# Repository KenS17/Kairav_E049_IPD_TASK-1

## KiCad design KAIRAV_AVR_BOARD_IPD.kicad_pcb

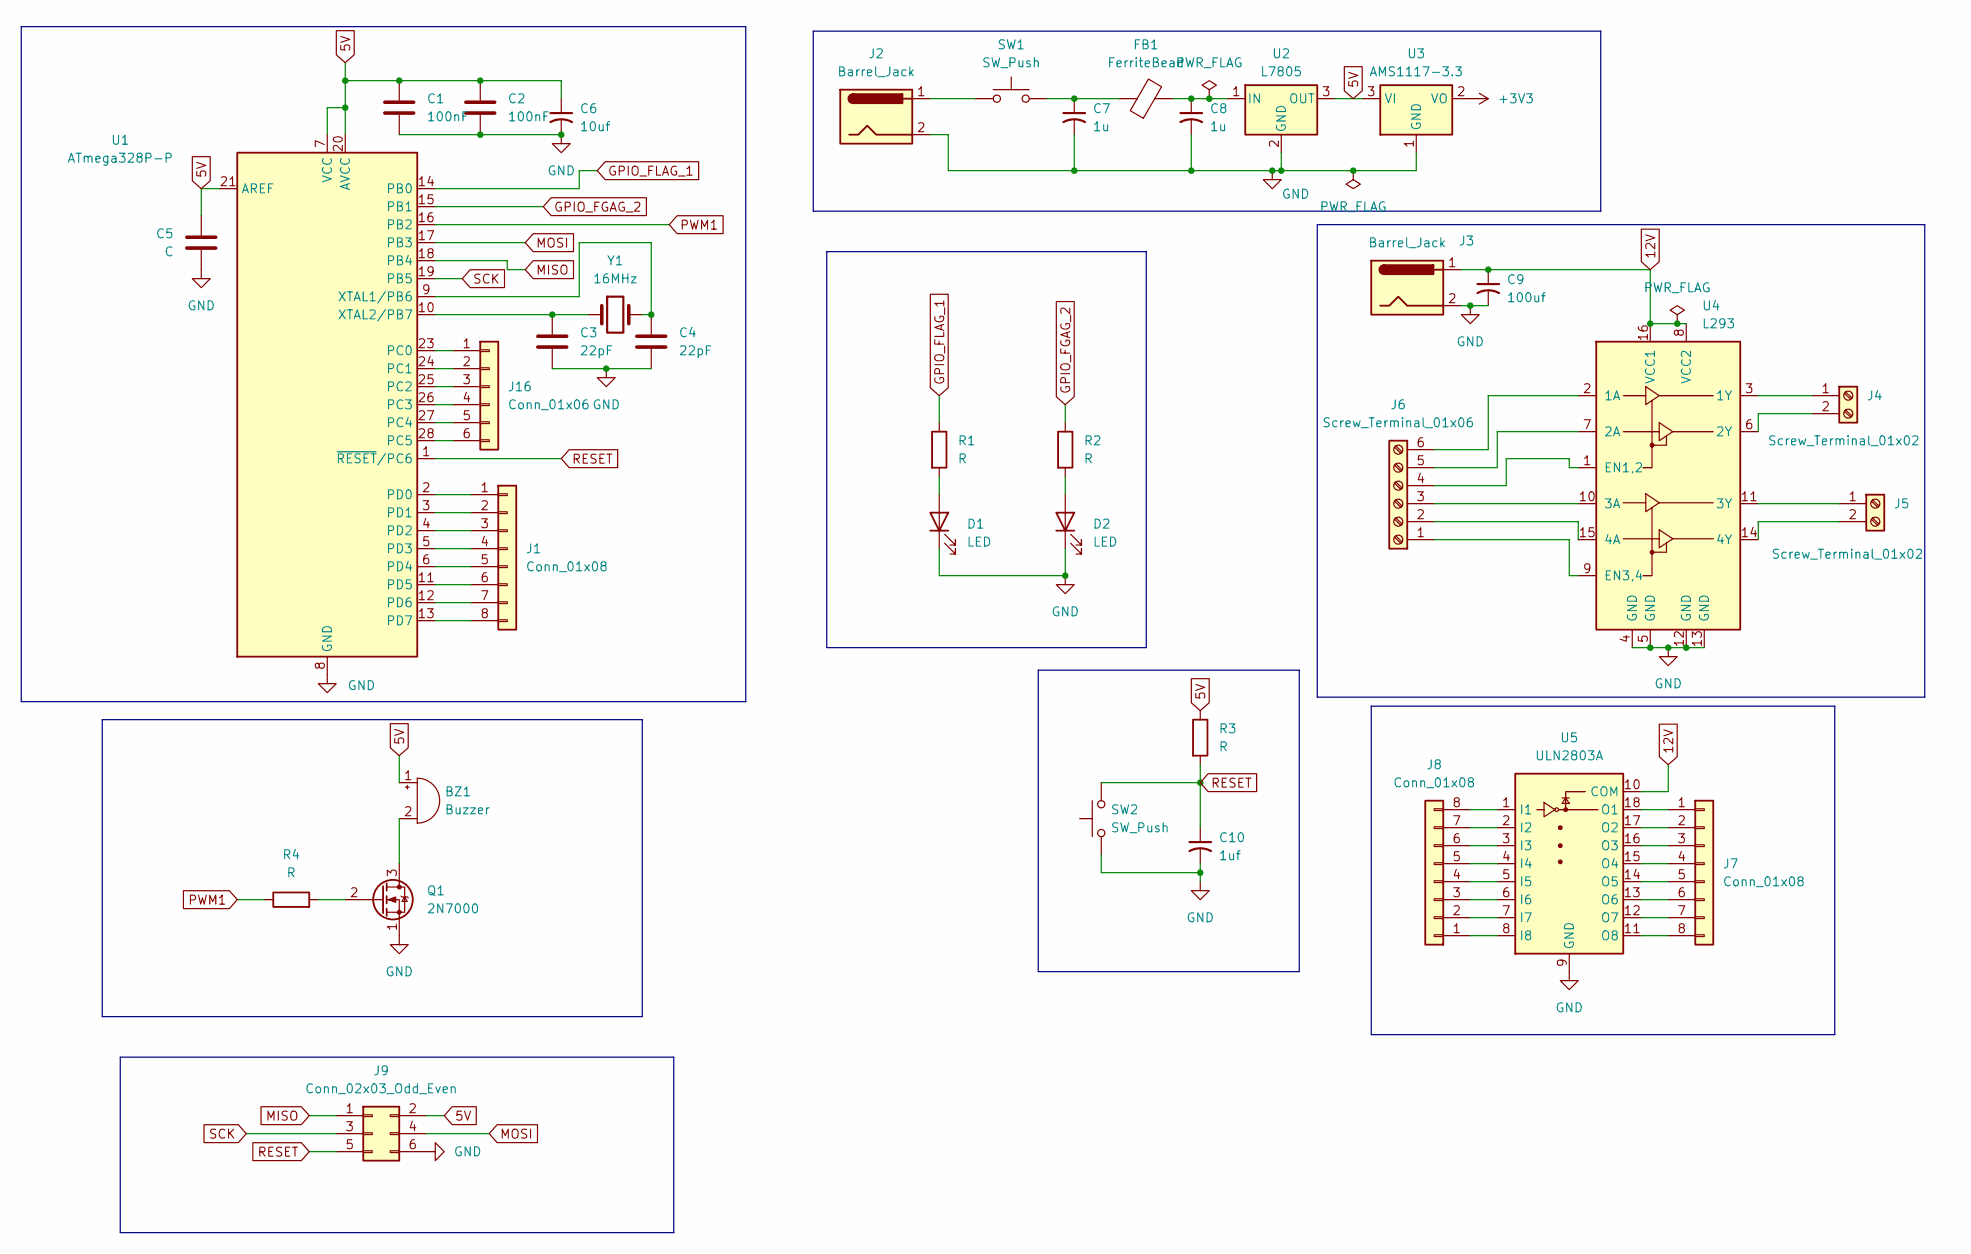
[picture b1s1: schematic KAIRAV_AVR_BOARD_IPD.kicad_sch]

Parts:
BZ1: Buzzer; Buzzer_12x9.5RM7.6
C1, C2: 100nF; C_Disc_D5.0mm_W2.5mm_P5.00mm
C3, C4: 22pF; C_Disc_D5.0mm_W2.5mm_P5.00mm
C5: C; C_Disc_D5.0mm_W2.5mm_P5.00mm
C6: 10uf; CP_Radial_D5.0mm_P2.00mm
C7, C8: 1u; C_Disc_D5.0mm_W2.5mm_P5.00mm
C9: 100uf; CP_Radial_D5.0mm_P2.00mm
C10: 1uf; C_Disc_D5.0mm_W2.5mm_P5.00mm
D1, D2: LED; LED_D5.0mm
FB1: FerriteBead; L_Axial_L7.0mm_D3.3mm_P10.16mm_Horizontal_Fastron_MICC
J1, J7, J8: Conn_01x08; PinHeader_1x08_P2.54mm_Vertical
J2, J3: Barrel_Jack; BarrelJack_Horizontal
J4, J5: Screw_Terminal_01x02; TerminalBlock_Phoenix_PT-1,5-2-3.5-H_1x02_P3.50mm_Horizontal
J6: Screw_Terminal_01x06; TerminalBlock_Phoenix_PT-1,5-6-3.5-H_1x06_P3.50mm_Horizontal
J9: Conn_02x03_Odd_Even; PinHeader_2x03_P2.54mm_Vertical
J16: Conn_01x06; PinHeader_1x06_P2.54mm_Vertical
Q1: 2N7000; TO-92_Inline
R1, R2, R3, R4: R; R_Axial_DIN0207_L6.3mm_D2.5mm_P7.62mm_Horizontal
SW1, SW2: SW_Push; SW_PUSH_6mm
U1: ATmega328P-P; DIP-28_W7.62mm
U2: L7805; TO-220-3_Vertical
U3: AMS1117-3.3; SOT-223-3_TabPin2
U4: L293; DIP-16_W7.62mm
U5: ULN2803A; DIP-18_W7.62mm
Y1: 16MHz; Crystal_HC49-U_Vertical

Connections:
5V: BZ1.1 (+), C1.1, C2.1, C5.2, C6.1, J9.2, R3.1, U1.7 (VCC), U1.20 (AVCC), U1.21 (AREF), U2.3 (OUT), U3.3 (VI)
12V: C9.1, J3.1, U4.8 (VCC2), U4.16 (VCC1), U5.10 (COM)
+3V3: U3.2 (VO)
GND: C1.2, C2.2, C3.2, C4.2, C5.1, C6.2, C7.2, C8.2, C9.2, C10.2, D1.1 (K), D2.1 (K), J2.2, J3.2, J9.6, Q1.1 (S), SW2.1, U1.8 (GND), U1.22 (GND), U2.2 (GND), U3.1 (GND), U4.4 (GND), U4.5 (GND), U4.12 (GND), U4.13 (GND), U5.9 (GND)
GPIO_FGAG_2: R2.1, U1.15 (PB1)
GPIO_FLAG_1: R1.1, U1.14 (PB0)
MISO: J9.1, U1.18 (PB4)
MOSI: J9.4, U1.17 (PB3)
unnamed: BZ1.2 (-), Q1.3 (D)
unnamed: C7.1, FB1.1, SW1.2
unnamed: D1.2 (A), R1.2
unnamed: D2.2 (A), R2.2
unnamed: J1.1, U1.2 (PD0)
unnamed: J1.2, U1.3 (PD1)
unnamed: J1.3, U1.4 (PD2)
unnamed: J1.4, U1.5 (PD3)
unnamed: J1.5, U1.6 (PD4)
unnamed: J1.6, U1.11 (PD5)
unnamed: J1.7, U1.12 (PD6)
unnamed: J1.8, U1.13 (PD7)
unnamed: J2.1, SW1.1
unnamed: J4.1, U4.3 (1Y)
unnamed: J4.2, U4.6 (2Y)
unnamed: J5.1, U4.11 (3Y)
unnamed: J5.2, U4.14 (4Y)
unnamed: J6.1, U4.9 (EN3,4)
unnamed: J6.2, U4.15 (4A)
unnamed: J6.3, U4.10 (3A)
unnamed: J6.4, U4.1 (EN1,2)
unnamed: J6.5, U4.7 (2A)
unnamed: J6.6, U4.2 (1A)
unnamed: J7.1, U5.18 (O1)
unnamed: J7.2, U5.17 (O2)
unnamed: J7.3, U5.16 (O3)
unnamed: J7.4, U5.15 (O4)
unnamed: J7.5, U5.14 (O5)
unnamed: J7.6, U5.13 (O6)
unnamed: J7.7, U5.12 (O7)
unnamed: J7.8, U5.11 (O8)
unnamed: J8.1, U5.8 (I8)
unnamed: J8.2, U5.7 (I7)
unnamed: J8.3, U5.6 (I6)
unnamed: J8.4, U5.5 (I5)
unnamed: J8.5, U5.4 (I4)
unnamed: J8.6, U5.3 (I3)
unnamed: J8.7, U5.2 (I2)
unnamed: J8.8, U5.1 (I1)
unnamed: J16.1, U1.23 (PC0)
unnamed: J16.2, U1.24 (PC1)
unnamed: J16.3, U1.25 (PC2)
unnamed: J16.4, U1.26 (PC3)
unnamed: J16.5, U1.27 (PC4)
unnamed: J16.6, U1.28 (PC5)
unnamed: Q1.2 (G), R4.2
unnamed: C4.1, U1.9 (XTAL1/PB6), Y1.2
unnamed: C3.1, U1.10 (XTAL2/PB7), Y1.1
unnamed: C8.1, FB1.2, U2.1 (IN)
PWM1: R4.1, U1.16 (PB2)
RESET: C10.1, J9.5, R3.2, SW2.2, U1.1 (~RESET/PC6)
SCK: J9.3, U1.19 (PB5)

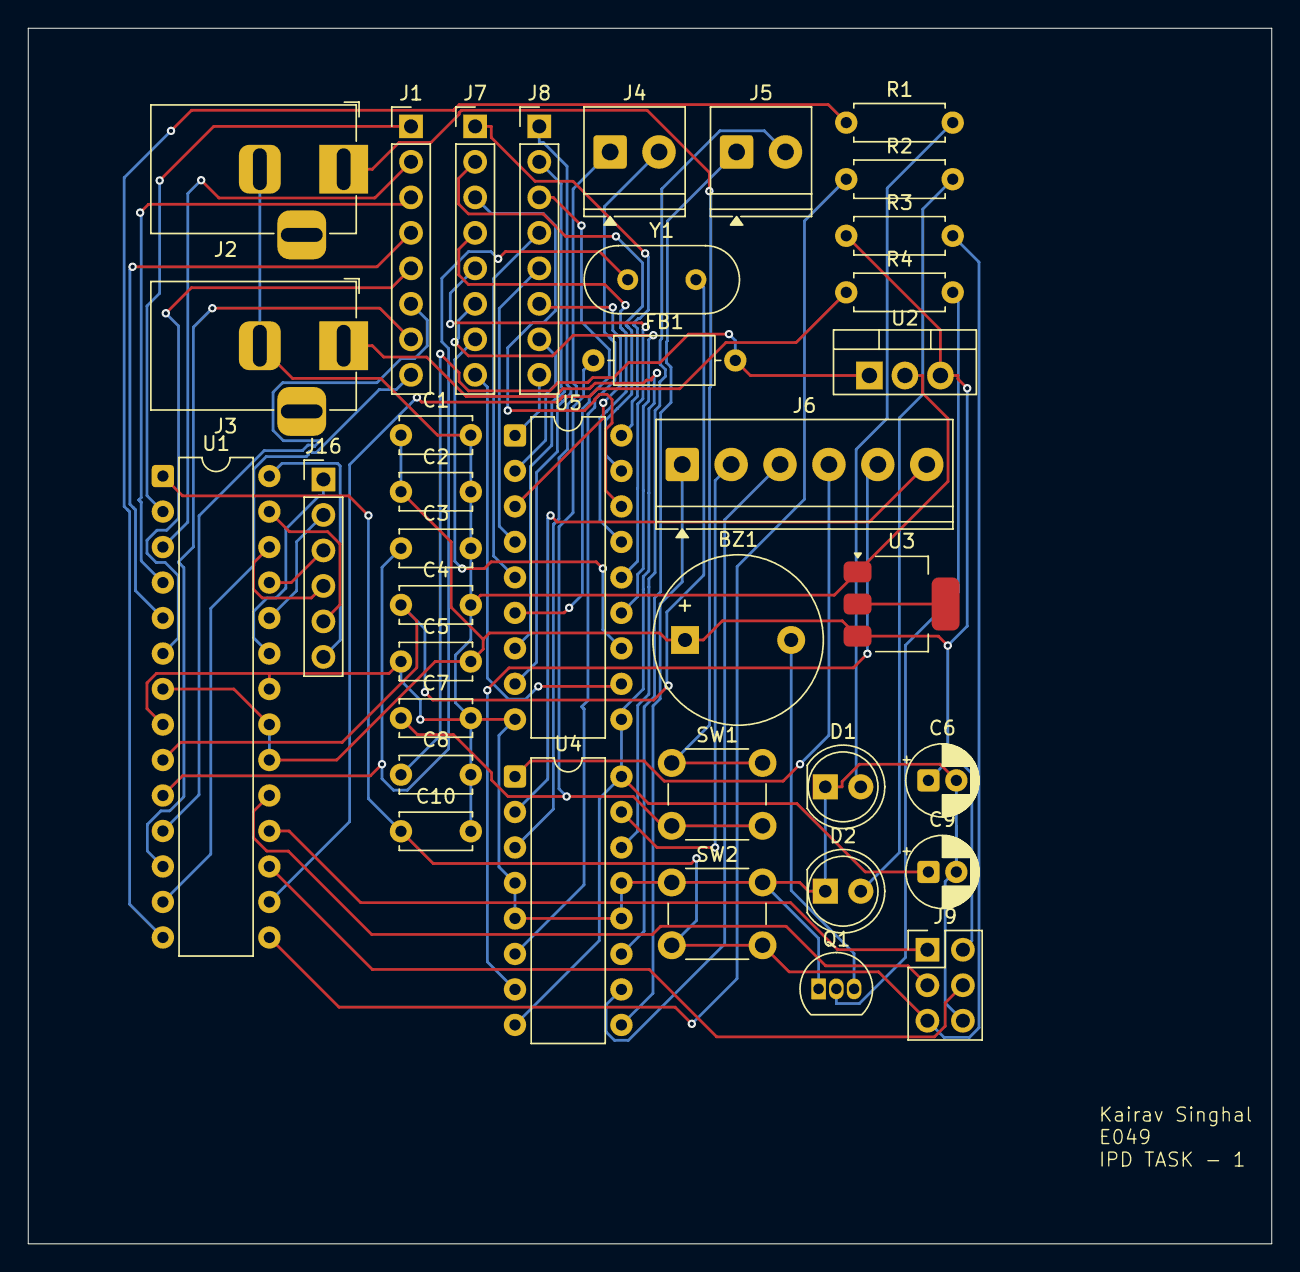
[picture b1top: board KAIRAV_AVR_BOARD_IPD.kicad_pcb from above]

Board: 2 copper layers, 89.0 x 87.0 mm, 37 parts (0 on the bottom side), 59 nets.
